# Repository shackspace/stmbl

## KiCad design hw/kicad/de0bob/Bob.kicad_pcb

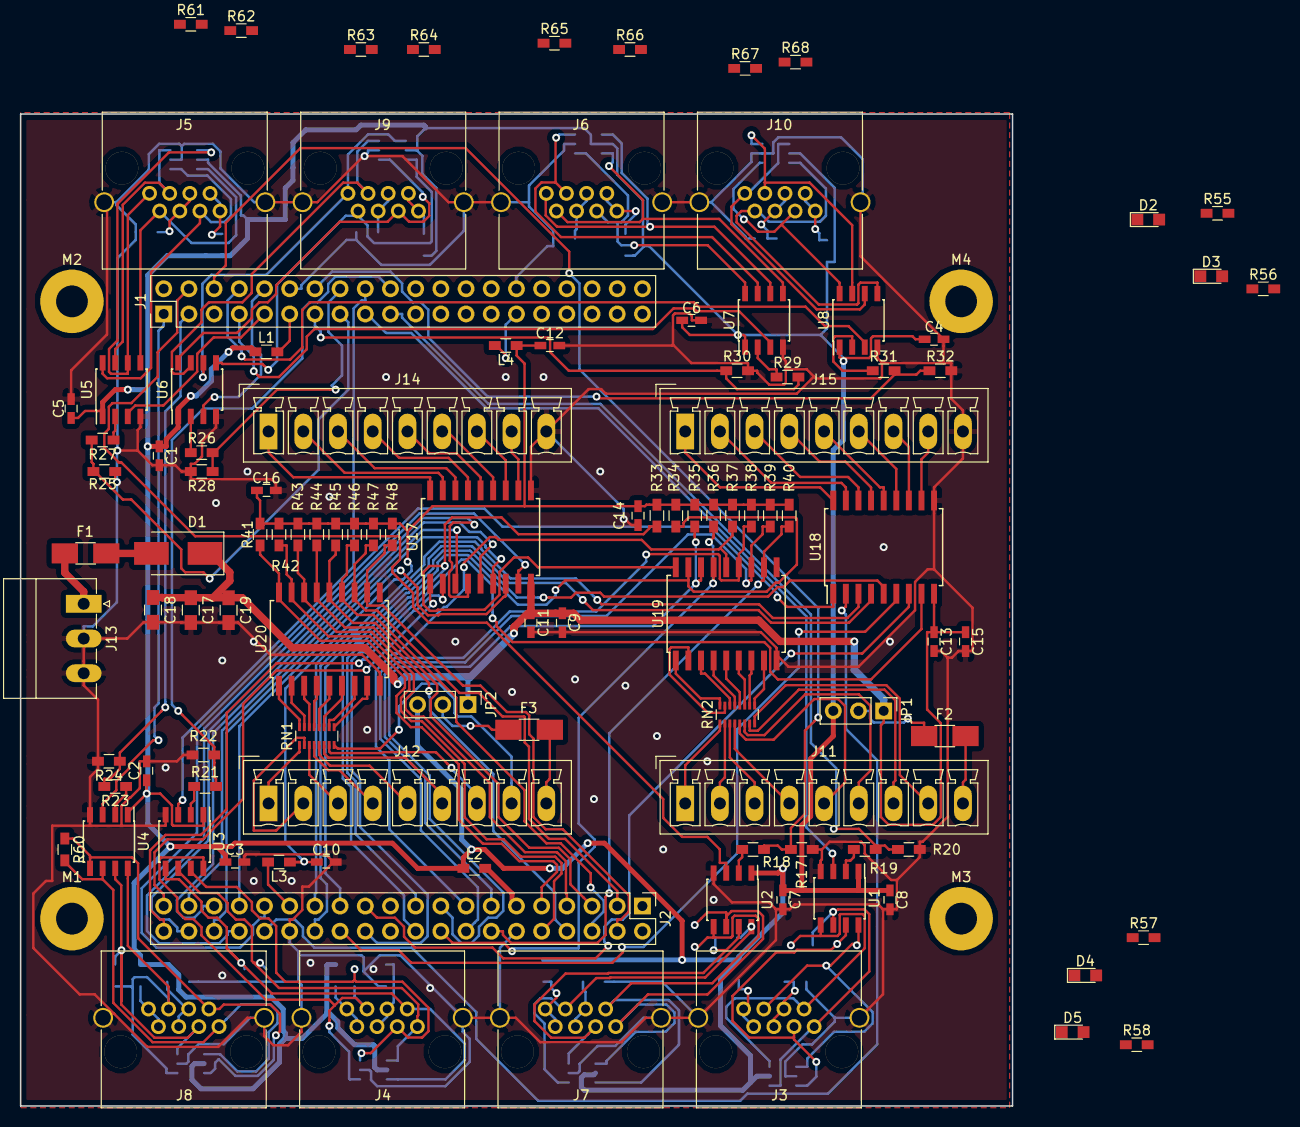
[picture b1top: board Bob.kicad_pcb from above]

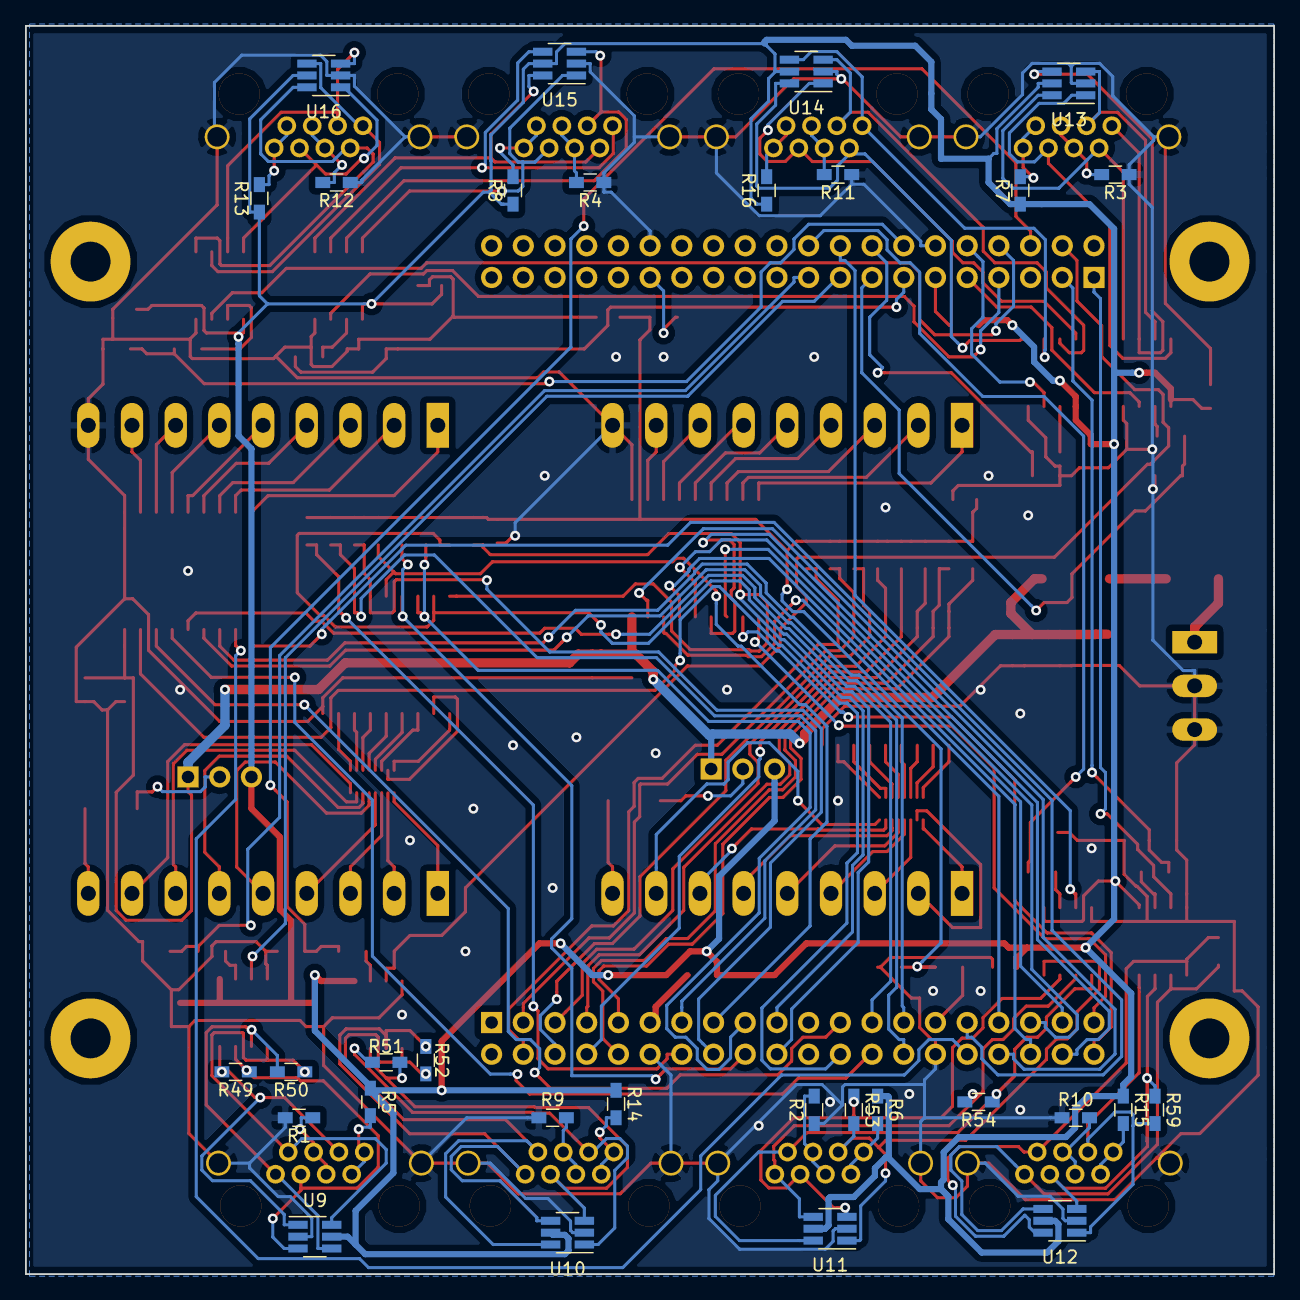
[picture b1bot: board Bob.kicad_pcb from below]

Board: 2 copper layers, 100.0 x 100.0 mm, 142 parts (31 on the bottom side), 174 nets.

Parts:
C1, C2, C3, C4, C5, C6, C7, C8, C9, C10, C11, C12, C13, C14, C15, C16: C; C_0603_HandSoldering
C17, C18, C19: C; C_0805_HandSoldering
D1: D; D_SMB_Handsoldering
D2, D3, D4, D5: LED; LED_0805
F1, F2, F3: Fuse; Fuse_SMD1206_HandSoldering
J1, J2: CONN_02X20; Pin_Header_Straight_2x20_Pitch2.54mm
J3, J4, J5, J6, J7, J8, J9, J10: RJ45
J11, J12, J14, J15: CONN_01X09; PhoenixContact_MCV-G_09x3.50mm_Vertical
J13: CONN_01X03; PhoenixContact_MC-G_03x3.50mm_Angled
JP1, JP2: Jumper_NC_Dual; Pin_Header_Straight_1x03_Pitch2.54mm
L1, L2, L3, L4: L_Small; R_0603_HandSoldering
M1, M2, M3, M4: MOUNT_3mm; MountingHole_3.2mm_M3_Pad
R1, R2, R5, R6, R9, R14: 0; R_0603_HandSoldering
R3, R4, R7, R8, R10, R11, R12, R13, R15, R16, R17, R18, R19, R20, R21, R22, R23, R24, R25, R26, R27, R28, R29, R30, R31, R32, R55, R56, R57, R58: R; R_0603_HandSoldering
R33, R34, R35, R36, R37, R38, R39, R40, R41, R42, R43, R44, R45, R46, R47, R48, R49, R50, R51, R52, R53, R54, R59, R60, R61, R62, R63, R64, R65, R66, R67, R68: 1k; R_0603_HandSoldering
RN1, RN2: R_Pack08; R_Array_Convex_8x0602
U1, U2, U3, U4, U5, U6, U7, U8: ADM4857; SOIC-8_3.9x4.9mm_Pitch1.27mm
U9, U10, U11, U12, U13, U14, U15, U16: USBLC6-4SC6; SOT-23-6_Handsoldering
U17, U18: TBD62783A; SOIC-18W_7.5x11.6mm_Pitch1.27mm
U19, U20: ULN2803ADWR; SOIC-18W_7.5x11.6mm_Pitch1.27mm

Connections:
+3V3: C10.1, C12.1, C14.1, C16.1, L3.1, L4.1, R33.1, R34.1, R35.1, R36.1, R37.1, R38.1, R39.1, R40.1, R41.1, R42.1, R43.1, R44.1, R45.1, R46.1, R47.1, R48.1, R55.1, R56.1, R57.1, R58.1
+5V: C1.1, C2.1, C3.1, C4.1, C5.1, C6.1, C7.1, C8.1, JP1.3, JP2.3, L1.1, L2.1, R5.1, R6.1, R7.1, R8.1, R13.1, R14.1, R15.1, R16.1, U1.1, U2.1, U3.1, U4.1, U5.1, U6.1, U7.1, U8.1, U9.5, U10.5, U11.5, U12.5, U13.5, U14.5, U15.5, U16.5
+24V: C9.1, C11.1, C13.1, C15.1, C17.1, C18.1, C19.1, D1.1, JP1.1, JP2.1, U17.9, U18.9
GND: C1.2, C2.2, C3.2, C4.2, C5.2, C6.2, C7.2, C8.2, C9.2, C10.2, C11.2, C12.2, C13.2, C14.2, C15.2, C16.2, C17.2, C18.2, C19.2, J1.12, J1.30, J2.12, J2.30, J3.9, J4.9, J5.9, J6.9, J7.9, J8.9, J9.9, J10.9, J13.2, J13.3, J14.9, J15.9, R1.2, R2.1, R3.1, R4.1, R9.1, R10.1, R11.1, R12.1, R17.2, R20.2, R22.2, R24.2, R25.2, R28.2, R30.2, R32.2, U1.4, U2.4, U3.4, U4.4, U5.4, U6.4, U7.4, U8.4, U9.2, U10.2, U11.2, U12.2, U13.2, U14.2, U15.2, U16.2, U17.10, U18.10, U19.9, U20.9
J1B0: J1.19, R19.2, R20.1
J1B1: J1.20, R21.2, R22.1
J1B2: J1.17, U1.3
J1B3: J1.18, U3.3
J1B4: J1.15, R25.1, R27.2
J1B5: J1.16, R26.2, R28.1
J1B6: J1.13, R29.2, R30.1
J1B7: J1.14, R31.2, R32.1
J1B8: J1.9, U5.3
J1B9: J1.10, U6.3
J1B10: J1.7, U7.3
J1B11: J1.8, U8.3
J1B13: J1.6, R17.1, R18.2
J1B14: J1.3, R23.2, R24.1
J1B15: J1.4, U2.3
J1B16: J1.1, U4.3
J3B0: J2.19, R33.2, U19.18
J3B1: J2.20, R34.2, U19.17
J3B2: J2.17, R35.2, U19.16
J3B3: J2.18, R36.2, U19.15
J3B4: J2.15, R37.2, U19.14
J3B5: J2.16, R38.2, U19.13
J3B6: J2.13, R39.2, U19.12
J3B7: J2.14, R40.2, U19.11
J3B8: J2.9, R41.2, U20.18
J3B9: J2.10, R42.2, U20.17
J3B10: J2.7, R43.2, U20.16
J3B11: J2.8, R44.2, U20.15
J3B12: J2.5, R45.2, U20.14
J3B13: J2.6, R46.2, U20.13
J3B14: J2.3, R47.2, U20.12
J3B15: J2.4, R48.2, U20.11
J4B0: J2.39, U17.1
J4B1: J2.40, U17.2
J4B2: J2.37, U17.3
J4B3: J2.38, U17.4
J4B4: J2.35, U17.5
J4B5: J2.36, U17.6
J4B6: J2.33, U17.7
J4B7: J2.34, U17.8
J4B8: J2.31, U18.1
J4B9: J2.32, U18.2
J4B10: J2.27, U18.3
J4B11: J2.28, U18.4
J4B12: J2.25, U18.5
J4B13: J2.26, U18.6
J4B14: J2.23, U18.7
J4B15: J2.24, U18.8
LED0: D2.1, J1.2
LED1: D3.1, J1.22
LED2: D4.1, J2.2
LED3: D5.1, J2.22
NRX0: J3.3, R49.1, U1.7, U9.3
NRX1: J7.3, R51.1, U2.7, U10.3
NRX2: J4.3, R53.1, U3.7, U11.3
NRX3: J8.3, R59.1, U4.7, U12.3
NRX4: J5.3, R61.1, U5.7, U13.3
NRX5: J9.3, R63.1, U6.7, U14.3
NRX6: J6.3, R65.1, U7.7, U15.3
NRX7: J10.3, R67.1, U8.7, U16.3
NTX0: J3.1, R50.2, U1.6, U9.4
NTX1: J7.1, R52.2, U2.6, U10.4
NTX2: J4.1, R54.2, U3.6, U11.4
NTX3: J8.1, R60.2, U4.6, U12.4
NTX4: J5.1, R62.2, U5.6, U13.4
NTX5: J9.1, R64.2, U6.6, U14.4
NTX6: J6.1, R66.2, U7.6, U15.4
NTX7: J10.1, R68.2, U8.6, U16.4
unnamed: D1.2, F1.2
unnamed: D2.2, R55.2
unnamed: D3.2, R56.2
unnamed: D4.2, R57.2
unnamed: D5.2, R58.2
unnamed: F1.1, J13.1
unnamed: F2.1, JP1.2
unnamed: F2.2, J11.9
unnamed: F3.1, JP2.2
unnamed: F3.2, J12.9
unnamed: J1.11, L1.2
unnamed: J1.29, L4.2
unnamed: J2.11, L2.2
unnamed: J2.29, L3.2
unnamed: J3.4, J3.5, R1.1
unnamed: J3.7, J3.8, R5.2
unnamed: J4.4, J4.5, R2.2
unnamed: J4.7, J4.8, R6.2
unnamed: J5.4, J5.5, R3.2
unnamed: J5.7, J5.8, R7.2
unnamed: J6.4, J6.5, R4.2
unnamed: J6.7, J6.8, R8.2
unnamed: J7.4, J7.5, R9.2
unnamed: J7.7, J7.8, R14.2
unnamed: J8.4, J8.5, R10.2
unnamed: J8.7, J8.8, R15.2
unnamed: J9.4, J9.5, R11.2
unnamed: J9.7, J9.8, R16.2
unnamed: J10.4, J10.5, R12.2
unnamed: J10.7, J10.8, R13.2
unnamed: J11.1, RN2.1
unnamed: J11.2, RN2.2
unnamed: J11.3, RN2.3
unnamed: J11.4, RN2.4
unnamed: J11.5, RN2.5
unnamed: J11.6, RN2.6
unnamed: J11.7, RN2.7
unnamed: J11.8, RN2.8
unnamed: J12.1, RN1.1
unnamed: J12.2, RN1.2
unnamed: J12.3, RN1.3
unnamed: J12.4, RN1.4
unnamed: J12.5, RN1.5
unnamed: J12.6, RN1.6
unnamed: J12.7, RN1.7
unnamed: J12.8, RN1.8
unnamed: J14.1, U17.18
unnamed: J14.2, U17.17
unnamed: J14.3, U17.16
unnamed: J14.4, U17.15
unnamed: J14.5, U17.14
unnamed: J14.6, U17.13
unnamed: J14.7, U17.12
unnamed: J14.8, U17.11
unnamed: J15.1, U18.18
unnamed: J15.2, U18.17
unnamed: J15.3, U18.16
unnamed: J15.4, U18.15
unnamed: J15.5, U18.14
unnamed: J15.6, U18.13
unnamed: J15.7, U18.12
unnamed: J15.8, U18.11
unnamed: R18.1, U2.2
unnamed: R19.1, U1.2
unnamed: R21.1, U3.2
unnamed: R23.1, U4.2
unnamed: R26.1, U6.2
unnamed: R27.1, U5.2
unnamed: R29.1, U7.2
unnamed: R31.1, U8.2
unnamed: RN1.9, U20.8
unnamed: RN1.10, U20.7
unnamed: RN1.11, U20.6
unnamed: RN1.12, U20.5
unnamed: RN1.13, U20.4
unnamed: RN1.14, U20.3
unnamed: RN1.15, U20.2
unnamed: RN1.16, U20.1
unnamed: RN2.9, U19.8
unnamed: RN2.10, U19.7
unnamed: RN2.11, U19.6
unnamed: RN2.12, U19.5
unnamed: RN2.13, U19.4
unnamed: RN2.14, U19.3
unnamed: RN2.15, U19.2
unnamed: RN2.16, U19.1
RX0: J3.6, R49.2, U1.8, U9.1
RX1: J7.6, R51.2, U2.8, U10.1
RX2: J4.6, R53.2, U3.8, U11.1
RX3: J8.6, R59.2, U4.8, U12.1
RX4: J5.6, R61.2, U5.8, U13.1
RX5: J9.6, R63.2, U6.8, U14.1
RX6: J6.6, R65.2, U7.8, U15.1
RX7: J10.6, R67.2, U8.8, U16.1
TX0: J3.2, R50.1, U1.5, U9.6
TX1: J7.2, R52.1, U2.5, U10.6
TX2: J4.2, R54.1, U3.5, U11.6
TX3: J8.2, R60.1, U4.5, U12.6
TX4: J5.2, R62.1, U5.5, U13.6
TX5: J9.2, R64.1, U6.5, U14.6
TX6: J6.2, R66.1, U7.5, U15.6
TX7: J10.2, R68.1, U8.5, U16.6

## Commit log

2017-07-17 added break out board for de0 nano soc with 8 sserial ports, 16 inputs, 16 outputs
2017-07-17 added status leds and terminators for sserial. layout unfinished
2017-07-18 finished routing. clean up pending.
